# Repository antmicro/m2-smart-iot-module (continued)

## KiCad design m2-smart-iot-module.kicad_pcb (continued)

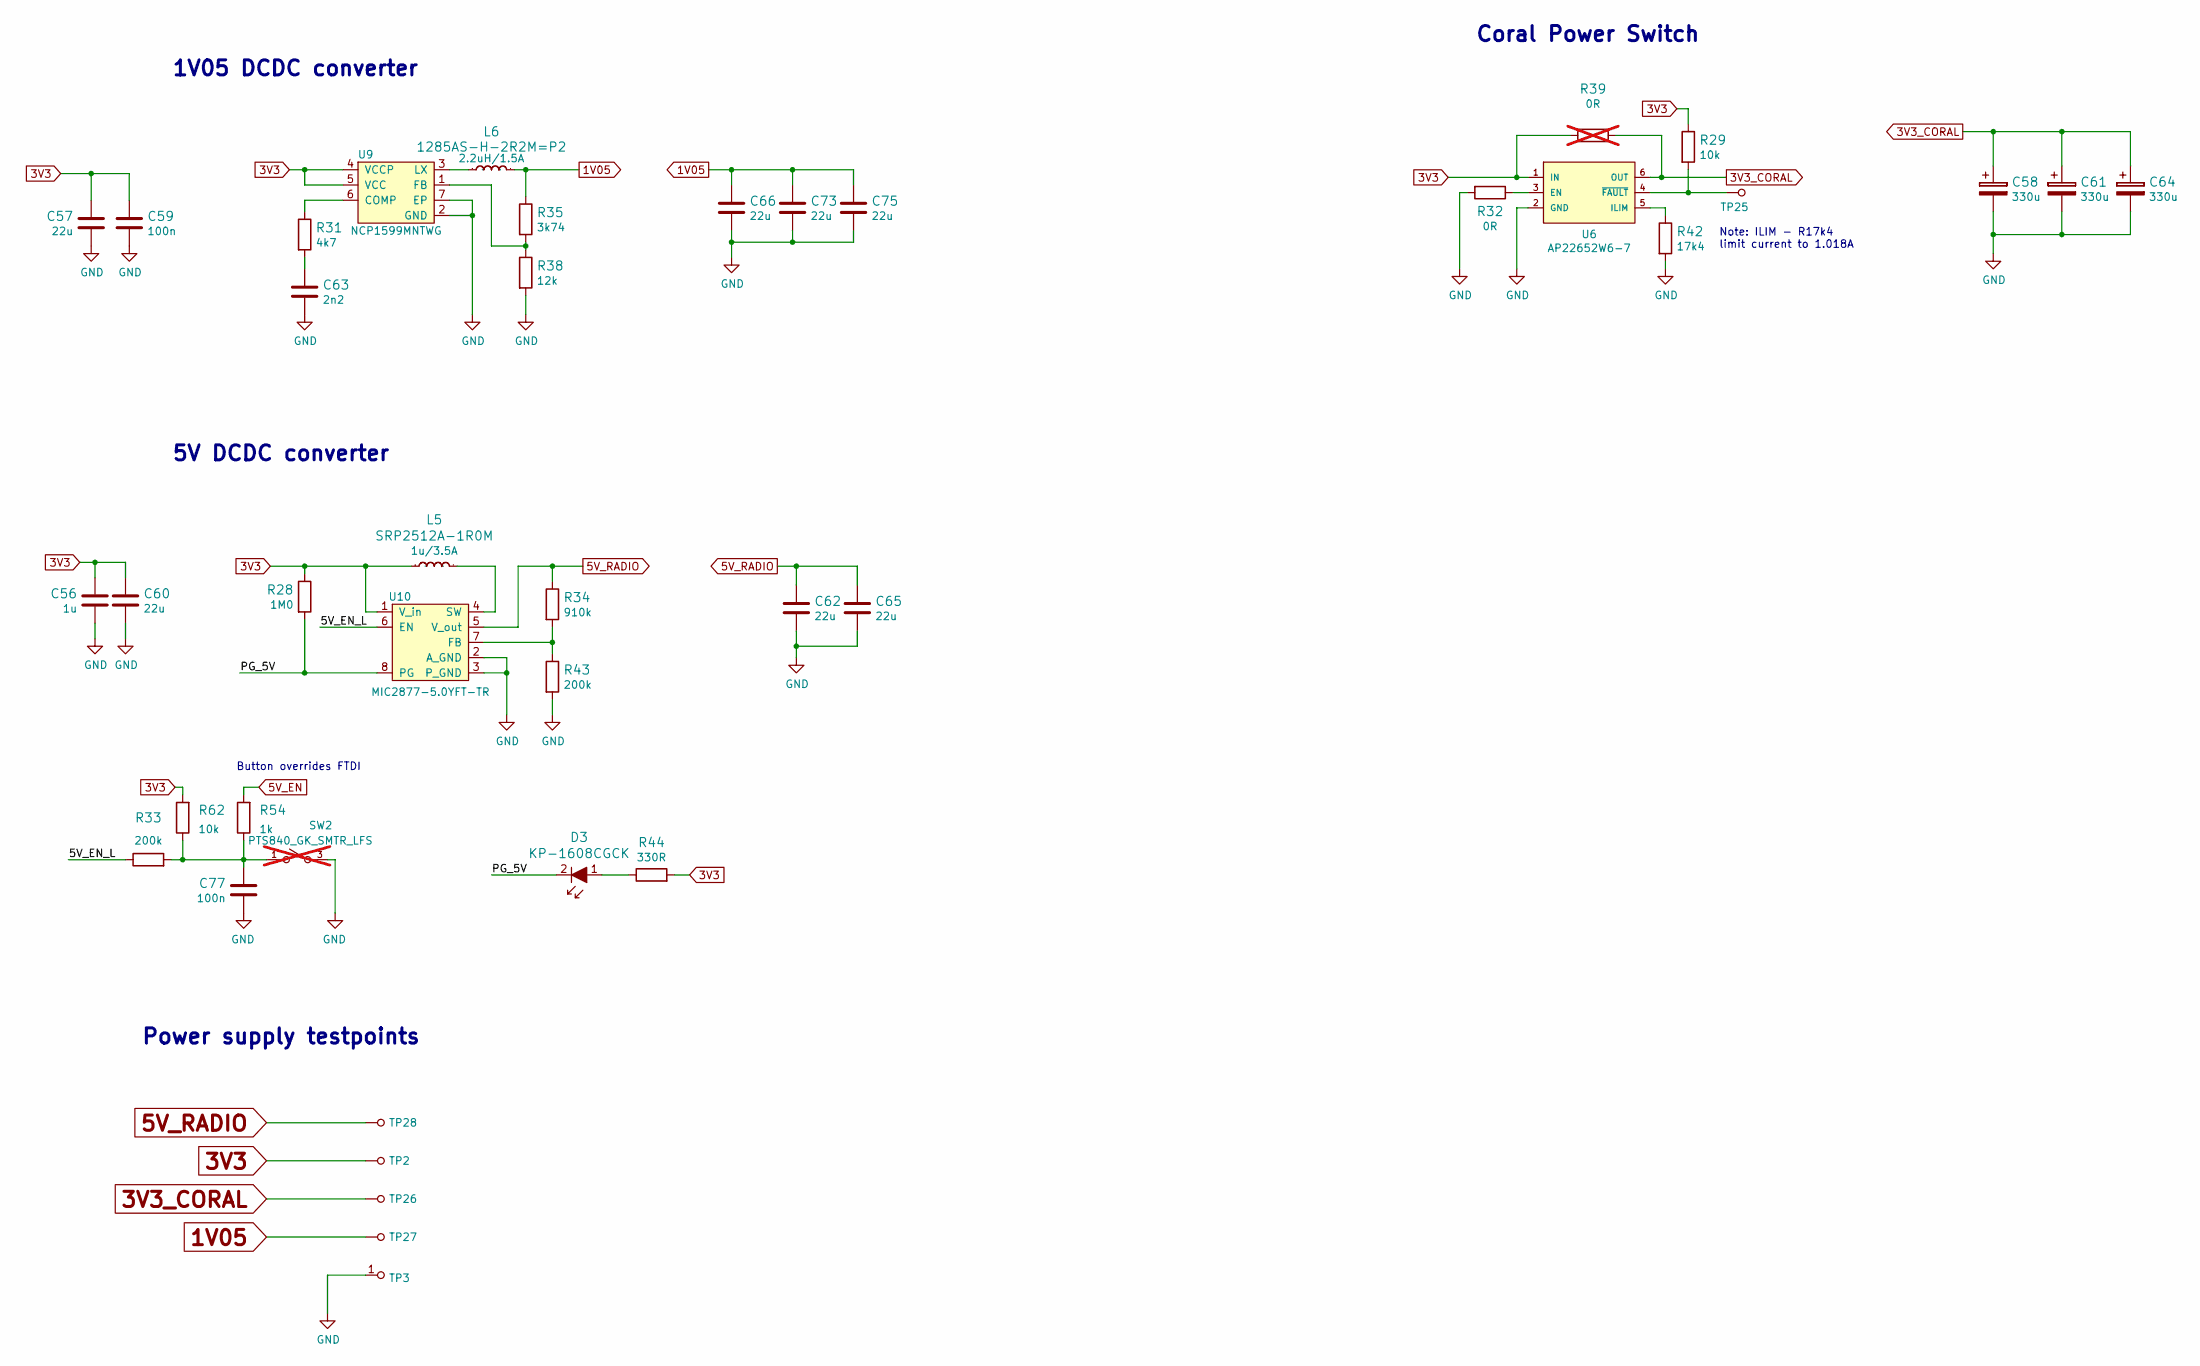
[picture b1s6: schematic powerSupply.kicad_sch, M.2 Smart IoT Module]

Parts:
C56: C_1u_0402; 0402-cap; MPN C1005X6S1A105K050BC
C57: C_22u_0603; 0603-cap; MPN GRM188R60J226MEA0D
C58, C61, C64: C_330u_EEF-SX; Panasonic_Electronic_Components-CD-0-0-MFG; MPN EEF-SX0G331ER
C59, C77: C_100n_0402; 0402-cap; MPN GRM155R61H104KE14D
C60, C62, C65, C66, C73, C75: C_22u_0805_10V; 0805-cap; MPN 0805ZD226MAT2A
C63: C_2n2_0402; 0402-cap; MPN C0402C222J5RACTU
D3: KP-1608CGCK; LED0603; MPN KP-1608CGCK
L5: SRP2512A-1R0M; MPN SRP2512A-1R0M
L6: 1285AS-H-2R2M=P2; 0805-res; MPN 1285AS-H-2R2M=P2
R28: R_1M0_0402; 0402-res; MPN CRG0402F1M0
R29, R62: R_10k_0402; 0402-res; MPN CRCW040210K0FKEDHP
R31: R_4k7_0402; 0402-res; MPN MCS04020C4701FE000
R32: R_0R_0402; 0402-res; MPN ERJ2GE0R00X
R33, R43: R_200k_0402; 0402-res; MPN RC0402FR-07200KL
R34: R_910k_0402; 0402-res; MPN CRCW0402910KFKED
R35: R_3k74_0402; 0402-res; MPN MCWR04X3741FTL
R38: R_12k_0402; 0402-res; MPN CRCW040212K0FKEDHP
R39: R_0R_0805; 0805-res; MPN CRCW08050000Z0EA; not fitted
R42: R_17k4_0402; 0402-res; MPN RC0402FR-0717K4L
R44: R_330R_0402; 0402-res; MPN ERJ2RKF3300X
R54: R_1k_0402; 0402-res; MPN CR0402-FX-1001GLF
SW2: PTS840_GK_SMTR_LFS; CK-PTS840_GK_SMTR_LFS-0; MPN PTS840 GK SMTR LFS; not fitted
TP2, TP25, TP26, TP27, TP28: TP_SMD1MM; Testpoint_smd_1mm
TP3: TP; TP-R-1.5
U6: AP22652W6-7; SOT-23-6; MPN AP22652W6-7
U9: NCP1599MNTWG; DFN-6_3x3mm_EP1; MPN NCP1599MNTWG
U10: MIC2877-5.0YFT-TR; FTQFN; MPN MIC2877-5.0YFT-TR

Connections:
1V05: C66.1, C73.1, C75.1, L6.2, R35.1, TP27.1; also elsewhere on the board
3V3: C56.1, C57.1, C59.1, C60.1, L5.1, R28.1, R29.1, R39.1, R44.2, R62.2, TP2.1, U6.1 (IN), U9.4 (VCCP), U9.5 (VCC), U10.1 (V_in); also elsewhere on the board
3V3_CORAL: C58.1, C61.1, C64.1, R39.2, TP26.1, U6.6 (OUT); also elsewhere on the board
5V_EN: R54.2; also elsewhere on the board
5V_RADIO: C62.1, C65.1, R34.1, TP28.1, U10.5 (V_out); also elsewhere on the board
/powerSupply/5V_EN_L: R33.1, U10.6 (EN)
/powerSupply/PG_5V: D3.2, R28.2, U10.8 (PG)
GND: C56.2, C57.2, C58.2, C59.2, C60.2, C61.2, C62.2, C63.2, C64.2, C65.2, C66.2, C73.2, C75.2, C77.2, R32.2, R38.2, R42.2, R43.2, SW2.3, SW2.4, TP3.1, U6.2 (GND), U9.2 (GND), U9.7 (EP), U10.2 (A_GND), U10.3 (P_GND); also elsewhere on the board
unnamed: C63.1, R31.2
unnamed: C77.1, R33.2, R54.1, R62.1, SW2.1, SW2.2
unnamed: D3.1, R44.1
unnamed: L5.2, U10.4 (SW)
unnamed: L6.1, U9.3 (LX)
unnamed: R29.2, TP25.1, U6.4 (~FAULT)
unnamed: R31.1, U9.6 (COMP)
unnamed: R32.1, U6.3 (EN)
unnamed: R34.2, R43.1, U10.7 (FB)
unnamed: R35.2, R38.1, U9.1 (FB)
unnamed: R42.1, U6.5 (ILIM)

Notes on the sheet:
Button overrides FTDI
Note: ILIM - R17k4 limit current to 1.018A
Coral Power Switch
5V DCDC converter
Power supply testpoints
1V05 DCDC converter

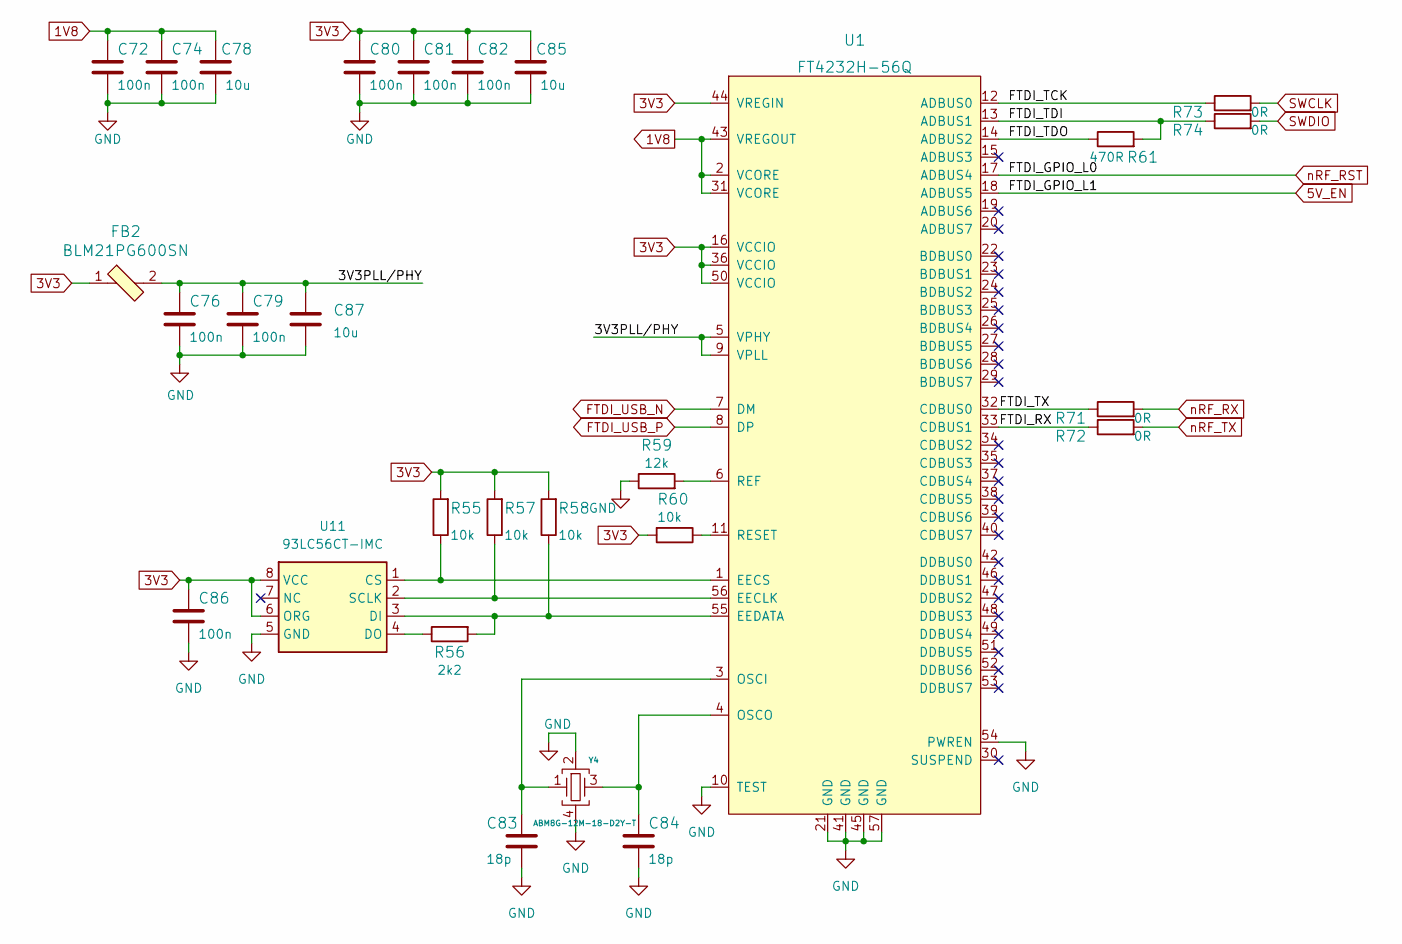
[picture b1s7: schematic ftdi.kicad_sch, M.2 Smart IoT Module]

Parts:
C72, C74, C76, C79, C80, C81, C82, C86: C_100n_0402; 0402-cap; MPN GRM155R61H104KE14D
C78, C85: C_10u_0805; 0805-cap; MPN 160R15X106KV4E
C83, C84: C_18p_0402; 0402-cap; MPN MC0402N180J500CT
C87: C_10u_0603; 0603-cap; MPN GRM188R61A106KE69D
FB2: BLM21PG600SN; 0805-res; MPN BLM21PG600SN1
R55, R57, R58, R60: R_10k_0402; 0402-res; MPN CRCW040210K0FKEDHP
R56: R_2k2_0402; 0402-res; MPN RC0402FR-072K2L
R59: R_12k_0402; 0402-res; MPN CRCW040212K0FKEDHP
R61: R_470R_0402; 0402-res; MPN CRCW0402470RFKED
R71, R72, R73, R74: R_0R_0402; 0402-res; MPN ERJ2GE0R00X
U1: FT4232H-56Q; QFN-56-1EP_8x8mm_P0.5mm_EP5.5.9x5.9mm; MPN FT4232H-56Q-REEL
U11: 93LC56CT-IMC; DFN-8_2x3mm; MPN 93LC56CT-IMC
Y4: ABM8G-12M-18-D2Y-T; KX-7; MPN ABM8G-12.000MHZ-18-D2Y-T

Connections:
1V8: C72.1, C74.1, C78.1, U1.2 (VCORE), U1.31 (VCORE), U1.43 (VREGOUT)
3V3: C80.1, C81.1, C82.1, C85.1, C86.1, FB2.1, R55.2, R57.2, R58.2, R60.2, U1.16 (VCCIO), U1.36 (VCCIO), U1.44 (VREGIN), U1.50 (VCCIO), U11.6 (ORG), U11.8 (VCC); also elsewhere on the board
5V_EN: U1.18 (ADBUS5); also elsewhere on the board
/FTDI/3V3PLL/PHY: C76.1, C79.1, C87.1, FB2.2, U1.5 (VPHY), U1.9 (VPLL)
/FTDI/FTDI_RX: R72.1, U1.33 (CDBUS1)
/FTDI/FTDI_TCK: R73.1, U1.12 (ADBUS0)
/FTDI/FTDI_TDI: R61.2, R74.1, U1.13 (ADBUS1)
/FTDI/FTDI_TDO: R61.1, U1.14 (ADBUS2)
/FTDI/FTDI_TX: R71.1, U1.32 (CDBUS0)
FTDI_USB_N: U1.7 (DM); also elsewhere on the board
FTDI_USB_P: U1.8 (DP); also elsewhere on the board
GND: C72.2, C74.2, C76.2, C78.2, C79.2, C80.2, C81.2, C82.2, C83.2, C84.2, C85.2, C86.2, C87.2, R59.1, U1.10 (TEST), U1.21 (GND), U1.41 (GND), U1.45 (GND), U1.54 (PWREN), U1.57 (GND), U11.5 (GND), Y4.2, Y4.4; also elsewhere on the board
unnamed: C83.1, U1.3 (OSCI), Y4.1
unnamed: C84.1, U1.4 (OSCO), Y4.3
unnamed: R55.1, U1.1 (EECS), U11.1 (CS)
unnamed: R56.1, U11.4 (DO)
unnamed: R56.2, R58.1, U1.55 (EEDATA), U11.3 (DI)
unnamed: R57.1, U1.56 (EECLK), U11.2 (SCLK)
unnamed: R59.2, U1.6 (REF)
unnamed: R60.1, U1.11 (RESET)
SWCLK: R73.2; also elsewhere on the board
SWDIO: R74.2; also elsewhere on the board
nRF_RST: U1.17 (ADBUS4); also elsewhere on the board
nRF_RX: R71.2; also elsewhere on the board
nRF_TX: R72.2; also elsewhere on the board

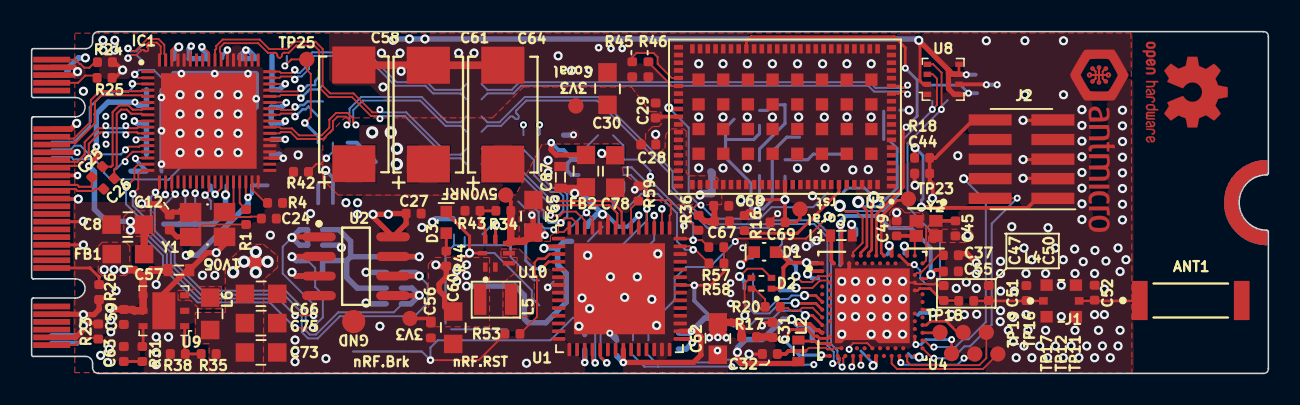
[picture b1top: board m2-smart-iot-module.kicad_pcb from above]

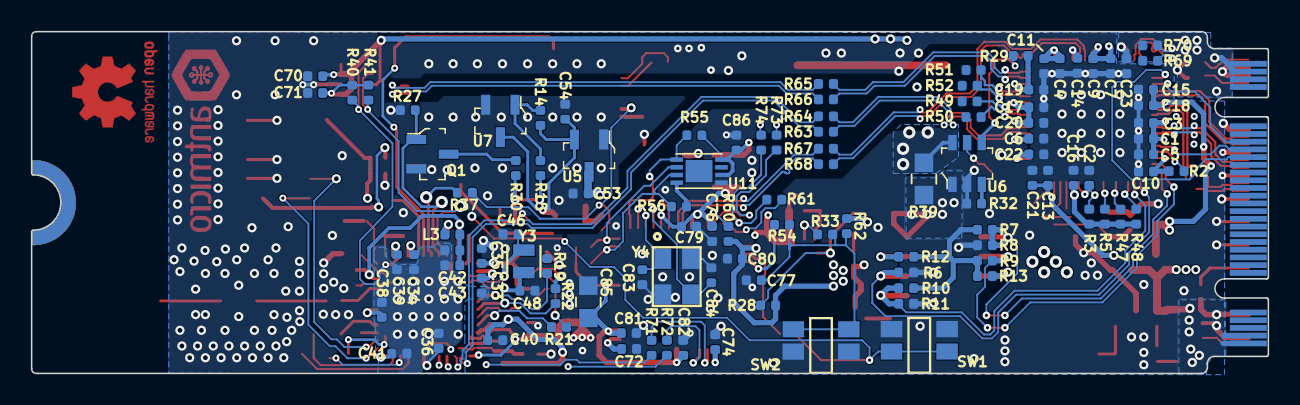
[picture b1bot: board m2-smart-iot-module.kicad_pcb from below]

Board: 4 copper layers, 80.1 x 22.2 mm, 212 parts (109 on the bottom side), 135 nets.

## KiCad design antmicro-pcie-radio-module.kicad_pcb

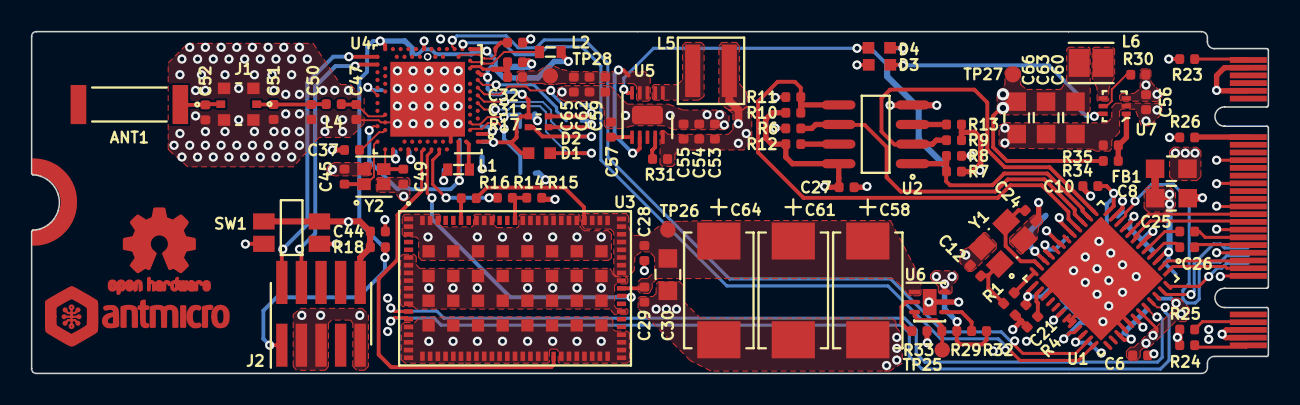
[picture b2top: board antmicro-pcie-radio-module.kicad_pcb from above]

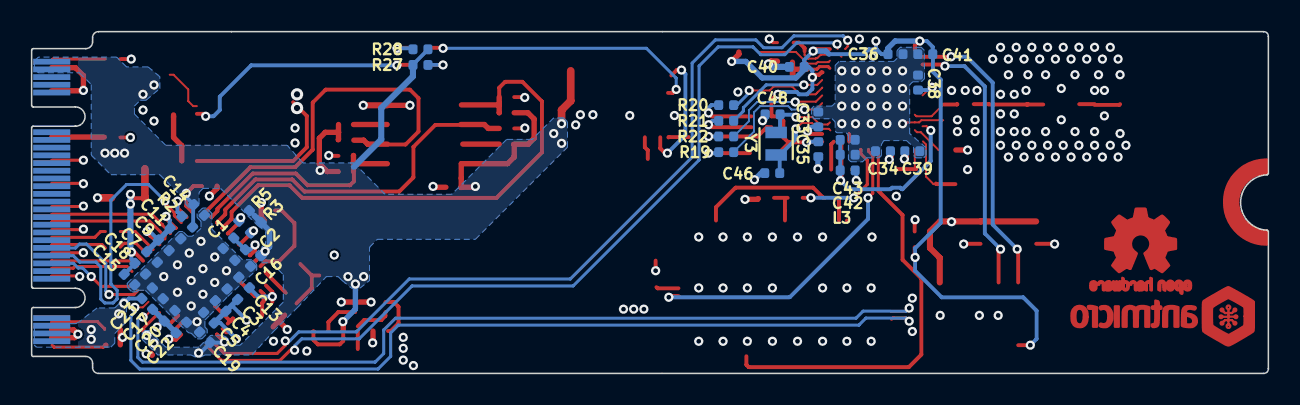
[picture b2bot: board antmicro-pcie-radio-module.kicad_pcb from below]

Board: 4 copper layers, 80.2 x 22.1 mm, 131 parts (41 on the bottom side), 86 nets.

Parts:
ANT1: ANT-2.45-CHP-T; Linx-ANT-2.45-CHP-T-MFG
C1, C3, C6, C7, C10, C13, C17, C18, C25, C26, C27, C28, C29, C33, C34, C36, C39, C41, C44: C_100n_0402; 0402-cap
C2, C4, C5, C9, C11, C14, C15, C16, C19, C20, C21, C22, C23, C57: C_10n_0402; 0402-cap
C8, C30: C_10u_0805; 0805-cap
C12, C24, C45, C49: C_8p_0402; 0402-cap
C31, C32, C40, C56: C_4u7_0402; 0402-cap
C35, C42: C_1u_0402; 0402-cap
C37: C_100p_0402; 0402-cap
C38: C_820p_0402; 0402-cap
C43: C_47n_0402; 0402-cap
C46, C48: C_12p_0402; 0402-cap
C47: C_0p8_0402; 0402-cap
C50: C_0p5_0402; 0402-cap
C51: RF_Capacitor; 0402-cap
C52: C_1p2_0402; 0402-cap
C53, C54, C55, C59, C62, C65: C_10u_0402; 0402-cap
C58, C61, C64: C_330u_EEF-SX; Panasonic_Electronic_Components-CD-0-0-MFG
C60, C63, C66: C_22u_0805_10V; 0805-cap
D1, D3, D4: KP-1608CGCK; LED0603
D2: APHF1608LSEEQBDZGKC; LED_APHF1608LSEEQBDZGKC
FB1: BLM21PG600SN; 0805-res
J1: MM8130-2600RA2; Murata-MM8130-2600RA2-MFG
J2: 2X05; ARM_SWD
J3: M.2-M+B-Pins; M.2 M+B Keys
L1: L_10u_250mA_0603; 0603-res
L2: L_10u_80mA_0603; 0603-res
L3: L_15n_0402; 0402-res
L4: L_4n7_0402; 0402-res
L5: XFL4020-102MEC; Coilcraft-XFL4020-0-0-MFG
L6: DFE201610E-1R0M=P2; Murata-DFE201610C-0-0-IPC_B
R1: R_680R_0402; 0402-res
R2, R3, R5, R6, R7, R8, R9, R10, R11, R12, R13, R18, R29: R_10k_0402; 0402-res
R4: R_1k6_0402; 0402-res
R14, R16: R_4k3_0402; 0402-res
R15: R_4k7_0402; 0402-res
R17: R_4R7_0402; 0402-res
R19, R27, R28: R_330R_0402; 0402-res
R20: R_2k2_0402; 0402-res
R21: R_390R_0402; 0402-res
R22: R_1k2_0402; 0402-res
R23, R24, R25, R26, R30, R31, R32: R_0R_0402; 0402-res
R33: R_21k_0402; 0402-res
R34: R_75k_0402; 0402-res
R35: R_100k_0402; 0402-res
SW1: PTS840_GK_SMTR_LFS; CK-PTS840_GK_SMTR_LFS-0
TP25, TP26, TP27, TP28: TP_SMD1MM; Testpoint_smd_1mm
U1: UPD720202; QFN48-Renesas-UPD720202
U2: SST25VF512A; SOIC8-SST25VF512A-33-4I-SAE-Level_B
U3: CoralAccelerator; MODULE_G313-06329-00
U4: NRF52840; Nordic_Semiconductor-NRF52840-QIAA-R-0-0-MFG
U5: TPS61232DRCR; VSON-10-1EP_3x3mm
U6: NCP380HMUAJAATBG; ON_Semiconductor-517AB-04_2013-C-IPC_B
U7: TLV62568PDRLT; SOT-563
Y1: NX3225SA-24M; NDK-NX3225SA-0-0-MFG
Y2: ABM11W-101-32.0000MHZ-T3; Abracon-ABM11W-0-0-0
Y3: ABS06-32.768KHZ-9-1-T; Abracon-ABS06-32.768KHZ-T-0

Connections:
1V05: C1.1, C2.1, C3.1, C4.1, C5.1, C7.1, C9.1, C11.1, C17.1, C20.1, C22.1, C60.1, C63.1, C66.1, L6.2, R34.1, TP27.1, U1.6, U1.9, U1.21, U1.30, U1.33, U1.39, U1.42
3V3: C6.1, C10.1, C14.1, C16.1, C19.1, C23.1, C27.1, C53.1, C54.1, C55.1, C56.1, FB1.1, J3.2, J3.4, J3.70, J3.72, J3.74, L5.1, R2.2, R3.2, R5.1, R7.1, R9.1, R10.1, R12.1, R13.1, R27.1, R28.1, R29.1, R30.1, R31.2, R32.2, U1.12, U1.22, U1.34, U1.43, U2.8, U5.10, U6.6, U7.3
3V3_CORAL: C28.1, C29.1, C30.1, C58.1, C61.1, C64.1, R16.1, TP26.1, U3.54, U3.56, U3.57, U3.58, U3.59, U3.60, U3.61, U3.62, U3.63, U3.64, U3.65, U3.66, U3.67, U6.1
5V_RADIO: C59.1, C62.1, C65.1, R17.1, TP28.1, U5.3, U5.4, U5.7
/M2-Pins/CFG0: J3.21, R26.1
/M2-Pins/CFG1: J3.69, R25.1
/M2-Pins/CFG2: J3.75, R24.1
/M2-Pins/CFG3: J3.1, R23.1
/nRF52840/DEC4_6: C42.1, C43.1, L3.2, U4.B5, U4.E24
/nRF52840/LED1: R19.2, U4.L1
/nRF52840/LED2_B: R21.2, U4.U1
/nRF52840/LED2_G: R20.2, U4.R1
/nRF52840/LED2_R: R22.2, U4.N1
/nRF52840/SWCLK: J2.4, U4.AA24
/nRF52840/SWDIO: J2.2, U4.AC24
/nRF52840/VDD: C35.1, C36.1, C39.1, C40.1, C41.1, D1.A, D2.1, J2.1, L2.2, R18.1, U4.A22, U4.AD2, U4.AD14, U4.AD23, U4.B1, U4.W1
/nRF52840/XC1: C45.1, U4.B24, Y2.1
/nRF52840/XC2: C49.1, U4.A23, Y2.3
/nRF52840/XL1: C46.1, U4.D2, Y3.1
/nRF52840/XL2: C48.1, U4.F2, Y3.2
/nRF52840/~RESET: C44.1, J2.10, R18.2, SW1.3, SW1.4, U4.AC13
/powerSupply/1V05_PG: D3.K, U7.6
/powerSupply/3V3_PG: D4.K, U5.5
CORAL_PGOOD: U3.37, U4.A14
CORAL_PMIC_EN: U3.53, U4.A12
CORAL_RST: R14.2, U4.A10
CORAL_USB_N: U1.45, U3.14
CORAL_USB_P: U1.44, U3.13
GND: C1.2, C2.2, C3.2, C4.2, C5.2, C6.2, C7.2, C8.2, C9.2, C10.2, C11.2, C12.2, C13.2, C14.2, C15.2, C16.2, C17.2, C18.2, C19.2, C20.2, C21.2, C22.2, C23.2, C24.2, C27.2, C28.2, C29.2, C30.2, C31.2, C32.2, C33.2, C34.2, C35.2, C36.2, C37.2, C38.2, C39.2, C40.2, C41.2, C42.2, C43.2, C44.2, C45.2, C46.2, C47.2, C48.2, C49.2, C50.2, C51.2, C52.2, C53.2, C54.2, C55.2, C56.2, C57.2, C58.2, C59.2, C60.2, C61.2, C62.2, C63.2, C64.2, C65.2, C66.2, J1.3, J1.4, J1.5, J1.6, J2.3, J2.5, J2.9, J3.3, J3.9, J3.27, J3.33, J3.39, J3.45, J3.51, J3.57, J3.71, J3.73, R4.2, R6.2, R8.2, R11.2, R15.2, R23.2, R24.2, R25.2, R26.2, R33.2, R35.2, SW1.1, SW1.2, U1.27, U1.31, U1.32, U1.40, U1.41, U1.49, U2.4, U3.1, U3.2, U3.3, U3.6, U3.7, U3.8, U3.9, U3.10, U3.11, U3.12, U3.15, U3.16, U3.17, U3.18, U3.19, U3.20, U3.21, U3.22, U3.23, U3.24, U3.25, U3.26, U3.27, U3.28, U3.29, U3.30, U3.31, U3.32, U3.33, U3.34, U3.35, U3.36, U3.38, U3.39, U3.40, U3.41, U3.42, U3.43, U3.44, U3.45, U3.46, U3.47, U3.48, U3.51, U3.55, U3.68, U3.69, U3.70, U3.71, U3.72, U3.73, U3.74, U3.75, U3.79, U3.80, U3.81, U3.86, U3.87, U3.88, U3.89, U3.90, U3.91, U3.92, U3.93, U3.94, U3.95, U3.96, U3.97, U3.98, U3.99, U3.100, U3.101, U3.102, U3.103, U3.104, U3.105, U3.106, U3.107, U3.108, U3.109, U3.110, U3.111, U3.112, U3.113, U3.114, U3.115, U3.116, U3.117, U3.118, U3.119, U3.120, U4.1, U4.B7, U4.F23, U5.11, U6.5, U6.7, U7.2, Y1.2, Y1.4, Y2.2, Y2.4
unnamed: ANT1.1, C52.1, J1.2
unnamed: C12.1, R1.1, Y1.1
unnamed: C8.1, C13.1, C15.1, C18.1, C21.1, FB1.2, U1.3, U1.25
unnamed: C24.1, U1.23, Y1.3
unnamed: C25.2, U1.5
unnamed: C26.2, U1.4
unnamed: C31.1, R17.2, U4.Y2
unnamed: C32.1, U4.AC5
unnamed: C33.1, U4.C1
unnamed: C34.1, U4.A18
unnamed: C37.1, U4.D23
unnamed: C38.1, U4.N24
unnamed: C47.1, L4.1, U4.H23
unnamed: C50.1, C51.1, J1.1, L4.2
unnamed: C57.1, U5.6
unnamed: D1.K, R19.1
unnamed: D2.2, R22.1
unnamed: D2.3, R21.1
unnamed: D2.4, R20.1
unnamed: D3.A, R27.2
unnamed: D4.A, R28.2
unnamed: L1.1, U4.B3
unnamed: L1.2, L3.1
unnamed: L2.1, U4.AB2
unnamed: L5.2, U5.1, U5.2
unnamed: L6.1, U7.4
unnamed: R1.2, U1.24
unnamed: R2.1, U1.11
unnamed: R3.1, U1.19
unnamed: R4.1, U1.26
unnamed: R5.2, U1.17
unnamed: R6.1, U1.15, U2.6
unnamed: R7.2, R8.1, U1.14, U2.1
unnamed: R9.2, U1.13, U2.2
unnamed: R10.2, R11.1, U1.16, U2.5
unnamed: R12.2, U2.7
unnamed: R13.2, U2.3
unnamed: R14.1, R15.1, U3.76
unnamed: R16.2, U3.83
unnamed: R29.2, TP25.1, U6.3
unnamed: R30.2, U7.5
unnamed: R31.1, U5.9
unnamed: R32.1, U6.4
unnamed: R33.1, U6.2
unnamed: R34.2, R35.1, U7.1
unnamed: U3.49, U3.50, U3.52, U3.84, U3.85
PECLK_N: J3.53, U1.2
PECLK_P: J3.55, U1.1
PERX_N: J3.41, U1.8
PERX_P: J3.43, U1.7
PETX_N: C25.1, J3.47
PETX_P: C26.1, J3.49
Radio_USB_N: U1.36, U4.AD4
Radio_USB_P: U1.35, U4.AD6
~PECREQ: J3.52, U1.10
~PERST: J3.50, U1.47
~PEWAKE: J3.54, U1.48

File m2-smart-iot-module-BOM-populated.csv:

Reference,Quantity,Value,Footprint,Manufacturer,MPN,InStorage,Remarks
ANT1,1,ANT-2.45-CHP-T,Linx-ANT-2.45-CHP-T-MFG,Linx,ANT-2.45-CHP-T,7,
C1 C3 C6 C7 C10 C13 C17 C18 C25 C26 C27 C28 C29 C33 C34 C36 C39 C41 C44 C67 C68 C69 C70 C71,24,C_100n_0402,0402-cap,Walsin,0402X104K6R3CT,110,
C12 C24 C45 C49,4,C_8p_0402,0402-cap,TDK,CGA2B2C0G1H080D050BA,20,
C2 C4 C5 C9 C11 C14 C15 C16 C19 C20 C21 C22 C23 C57,14,C_10n_0402,0402-cap,AVX,04025G103ZAT2A,70,
C31 C32 C40 C56,4,C_4u7_0402,0402-cap,MURATA,GRM155R61A475MEAAD,20,
C35 C42,2,C_1u_0402,0402-cap,TDK,C1005X6S1A105K050BC,0,
C37,1,C_100p_0402,0402-cap,WALSIN,0402N101J500CT,10,
C38,1,C_820p_0402,0402-cap,TDK,CGA2B2C0G1H821J050BA ,10,
C43,1,C_47n_0402,0402-cap,MULTICOMP,MC0402X473K160CT,10,
C46 C48,2,C_12p_0402,0402-cap,TDK,ERJ2GE0R00X,10,
C47,1,C_0p8_0402,0402-cap,Murata,GJM1555C1HR80WB01D ,10,
C50,1,C_0p5_0402,0402-cap,Murata,GJM1555C1HR50WB01D,10,
C51,1,RF_Capacitor,0402-cap,-,-,0,
C52,1,C_1p2_0402,0402-cap,Murata,GJM1555C1H1R2WB01D,10,
C53 C54 C55 C59 C62 C65,6,C_10u_0402,0402-cap,MURATA,GRM155R60J106ME44D,30,
C58 C61 C64,3,C_330u_EEF-SX,Panasonic_Electronic_Components-CD-0-0-MFG,PANASONIC,EEF-SX0G331ER,20,
C60 C63 C66,3,C_22u_0805_10V,0805-cap,AVX,0805ZD226MAT2A,15,
C8 C30,2,C_10u_0805,0805-cap,JOHANSON_DIELECTRICS,160R15X106KV4E,0,
D1 D3 D4,3,KP-1608CGCK,LED0603,KINGBRIGHT,KP-1608CGCK,15,
D2,1,APHF1608LSEEQBDZGKC,LED_APHF1608LSEEQBDZGKC,Kingbright,APHF1608LSEEQBDZGKC,10,
FB1,1,BLM21PG600SN,0805-res,Murata Electronics North America,BLM21PG600SN1,10,
J1,1,MM8130-2600RA2,Murata-MM8130-2600RA2-MFG,Murata,MM8130-2600RA2 ,10,
J2,1,2X05,ARM_SWD,Samtec,SHF-105-01-L-D-SM,5,
J3,1,M.2-M+B-Pins,M.2-M+B-Keys,,,0,
L1,1,L_10u_250mA_0603,0603-res,TDK,MLZ1608M100WTD25,10,
L2,1,L_10u_80mA_0603,0603-res,Taiyo Yuden,LBMF1608T100K,25,
L3,1,L_15n_0402,0402-res,Taiyo Yuden,HK100515NJ-T,25,
L4,1,L_4n7_0402,0402-res,MULTICOMP PRO,MCFT000004 ,10,
L5,1,XFL4020-102MEC,Coilcraft-XFL4020-0-0-MFG,Coilcraft,XFL4020-102MEC,5,
L6,1,DFE201610E-1R0M=P2,Murata-DFE201610C-0-0-IPC_B,Murata,DFE201610E-1R0M=P2,5,
MP1,1,PCB_Mount_Hole_M2,M.2-Stud,,,0,
R1,1,R_680R_0402,0402-res,MULTICOMP PRO,MCWR04X6800FTL,10,
R16,1,R_8k2_0402,0402-res,PANASONIC,ERJ2RKF8201X,0,
R17,1,R_4R7_0402,0402-res,PANASONIC,ERJ2GEJ4R7X ,0,
R19 R27 R28,3,R_330R_0402,0402-res,PANASONIC,ERJ2RKF3300X ,20,
R2 R3 R5 R6 R7 R9 R10 R12 R13 R18 R29 R31 R38,13,R_10k_0402,0402-res,VISHAY,CRCW040210K0FKEDHP,70,
R20 R40 R41,3,R_2k2_0402,0402-res,YAGEO,RC0402FR-072K2L,0,
R21,1,R_390R_0402,0402-res,PANASONIC,ERJ2RKF3900X ,20,
R22,1,R_1k2_0402,0402-res,PANASONIC_ELECTRONIC_COMPONENTS,ERJ2RKF1201X,10,
R23 R24 R25 R26 R30 R32,6,R_0R_0402,0402-res,PANASONIC,ERJ2GE0R00X,30,
R33,1,R_21k_0402,0402-res,PANASONIC,ERJ2RKF2102X ,10,
R34,1,R_75k_0402,0402-res,MULTICOMP,MCWR04X7502FTL,10,
R35 R36,2,R_100k_0402,0402-res,VISHAY,CRCW0402100KFKEDHP,10,Different manufacturer (TE CONNECTIVITY)
R4,1,R_1k6_0402,0402-res,MULTICOMP PRO,MCWR04X1601FTL ,10,
SW1 SW2,2,PTS840_GK_SMTR_LFS,CK-PTS840_GK_SMTR_LFS-0,CK,PTS840 GK SMTR LFS,10,
U1,1,UPD720202,QFN48-Renesas-UPD720202,Renesas,UPD720202K8-701-BAA-A,10,
U2,1,SST25VF512A,SOIC8-SST25VF512A-33-4I-SAE-Level_B,Microchip,SST25VF512A-33-4I-SAE,5,
U3,1,CoralAccelerator,MODULE_G313-06329-00,Coral,G313-06329-00,9,
U4 U4,2,NRF52840,Nordic_Semiconductor-NRF52840-QIAA-R-0-0-MFG,Nordic Semiconductor,NRF52840-QIAA-R,10,
U5,1,TPS61232DRCR,VSON-10-1EP_3x3mm,Texas Instruments,TPS61232DRCR,0,
U6,1,NCP380HMUAJAATBG,ON_Semiconductor-517AB-04_2013-C-IPC_B,ON Semiconductor,NCP380HMUAJAATBG,0,
U7,1,TLV62568PDRLT,SOT-563,Texas Instruments,TLV62568PDRLT,25,
U8,1,BME280,Pressure_Sensor_LGA-8_2.5x2.5mm_BME280,Bosch Sensortec,BME280,0,
Y1,1,NX3225SA-24M,NDK-NX3225SA-0-0-MFG,NDK,NX3225SA-24.000M-STD-CSR-3 ,0,
Y2,1,ABM11W-101-32.0000MHZ-T3,Abracon-ABM11W-0-0-0,ABRACON,ABM11W-101-32.0000MHZ-T3,10,
Y3,1,ABS06-32.768KHZ-9-1-T,Abracon-ABS06-32.768KHZ-T-0,ABRACON,ABS06-32.768KHZ-9-1-T,5,

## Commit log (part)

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2021-08-11 Add PCIe/USB controller
2021-08-11 Add initial mechanical mock
2021-08-11 Add M.2 B+M edge connector
2021-08-11 Initial work on RF part
2021-08-11 Update U.FL model, fix library links
2021-08-11 Add IOs
2021-08-11 Add power supply circuitry
2021-08-11 Finishing schematics, RF part left
2021-08-11 Add RF path
2021-08-11 Update naming convention
2021-08-11 Add changes after pre-production review.
2021-08-11 Add initial component layout
2021-08-11 Layout: add signal traces
2021-08-11 Add BME280
2021-08-11 Add block diagram
2021-08-11 Resolve DRC
2021-08-11 Cleanup
2021-08-11 Layout: add power planes
2021-08-11 Update schematic format
2021-08-11 Add README
2021-10-19 revised BOM
2021-12-16 Notes added by 'git notes add'
2022-03-18 Cleaned first 3 schematic sheets; Started fixing schematics after rev 1.0.0 bringup
2022-03-21 Added Coral RESET circuitry
2022-03-22 Changed DCDC converter to available ones
2022-03-22 Initial new components placement on PCB (After changes from rev 1.0.0
2022-03-22 Fixed USBSEL pullup, missing connection on DCDC cap
2022-03-22 Routed PCIe, rev bumped to 1.1.0
2022-03-25 Finish routing - no unconnected nets, DRC almost clear
2022-03-25 Route R16 (change from schematic)
2022-03-25 Designator cleanup, update revision info
2022-03-28 Reference designators position correction
2022-03-28 Labels position corrections
2022-03-29 Added 0R DNP to pins 49, 50.
2022-03-29 Rearrangement of JTAG connector and U8 sensor
2022-03-29 Moved antenna out of GND plane
2022-03-30 Updated width and gap of USB and PCIe lanes to correct impedance
2022-03-30 Added stackup table to PCB
2022-03-31 Added spreadsheet with power consumption
2022-03-31 Added 3d models of BME280 and 1V05 DCDC
2022-04-07 Silkscreen improvements, removed DRC errors on M.2 connector
2022-04-07 Adjust position of C56, add GND via near C56 and C60
2022-07-08 Switched USB controller
2022-07-08 Added FTDI schematic
2022-07-11 Added comments to schematic
2022-07-11 Created FT2232 layout
2022-07-11 Bumped minor version
2022-07-11 Moved button to bottom
2022-07-11 Bumped version to 1.2.1
2022-07-11 Layout touch-ups
2022-07-11 Bumped version to 1.2.2
2022-07-12 Fixed SWD
2022-07-12 Bumped version
2022-07-12 Cleanup, fix ignore
2022-07-15 Applied fixes to issues that came up in review
2022-07-15 Bumped version to 1.2.4
2022-08-19 Fixed silkscreen
2022-08-19 Bump revision to 1.2.6
2022-08-19 Clear silks
2022-08-19 Bump revision to 1.2.5
2022-08-19 Place NRF52 reset via in empty space between AC9 and AC5
2022-08-19 Cleanup old version files
2022-08-19 Fix DRC
2022-08-19 Replaced ft2232 with ft4232H
2022-08-19 Bump revision to 1.2.7
2022-08-19 Migrated Project Symobl Library to KiCad6 format
    The old KiCad 5.x project libraries in conjunction with KiCad 6 project files
    cause kmake bom and others to fail and throw errors
2022-08-19 Cleanup after library migration
2022-08-19 Loclib
2022-08-19 Change net class names to be ok with convention
2022-08-19 Add OR resistors to outputs of the PCIE-USB bridge and FTDI
2022-08-19 Remove kicad_prl file
2022-08-19 Add resistors to PCB, adjust routing, clear silks
2022-08-19 Ported to pcbway stackup
2022-08-19 Bump revision to 1.2.9
2022-08-19 Rev bump to 1.2.8
2022-08-19 Remove .pretty footprint library. Remove sym_bak file
2022-08-19 Rewrite README to .md, restore images
2022-08-19 Update date in LICENSE
2022-08-22 Add schematic
